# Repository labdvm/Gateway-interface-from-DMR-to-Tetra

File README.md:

# Gateway-interface-from-DMR-to-Tetra
Gateway interface from DMR mobile radio to Tetra MTM5400, Motorola radios
DMR radio communication is via Simplex-Hotspot connect to Brandmeister and DMR RF power should be lowest as possible.
V 1.1
Z32IT

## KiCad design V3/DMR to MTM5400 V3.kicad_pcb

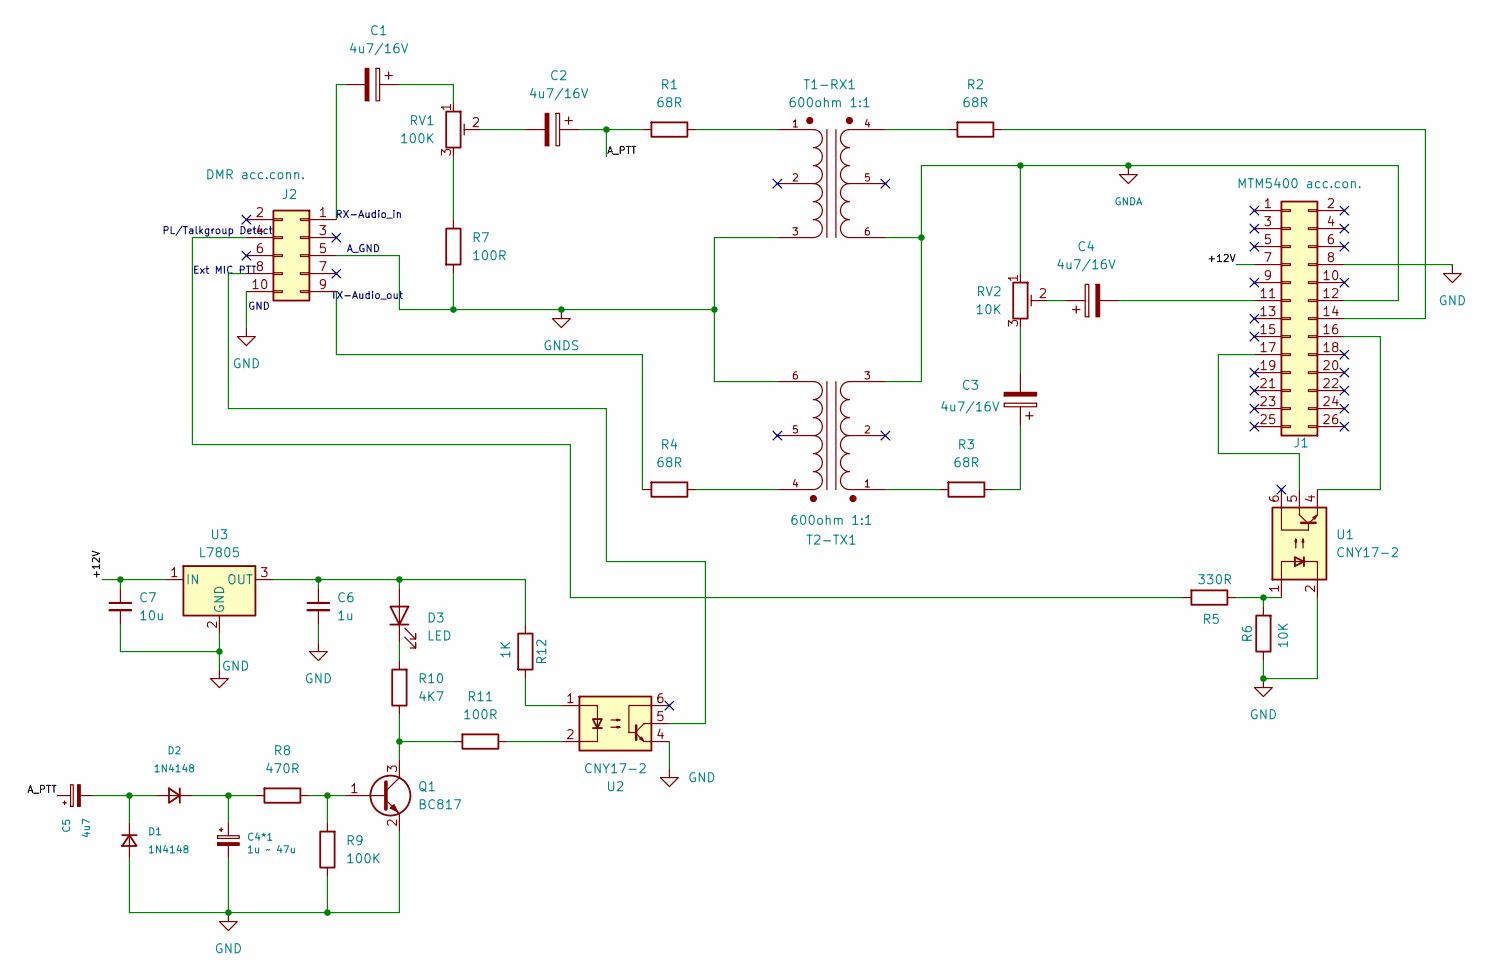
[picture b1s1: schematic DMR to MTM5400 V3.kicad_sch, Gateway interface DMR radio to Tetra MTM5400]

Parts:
C1, C2, C3, C4: 4u7/16V; CP_EIA-3216-12_Kemet-S
C4*1: 1u ~ 47u; CP_EIA-3216-12_Kemet-S
C5: 4u7; CP_EIA-3216-12_Kemet-S
C6: 1u; C_1206_3216Metric
C7: 10u; C_1206_3216Metric
D1, D2: 1N4148; D_SOD-123
D3: LED; LED_1206_3216Metric
J1: MTM5400 acc.con.; MTM5400_1
J2: DMR acc.conn.; PinHeader_2x05_P2.54mm_Vertical
Q1: BC817; SOT-23
R1, R2, R3, R4: 68R; R_1206_3216Metric
R5: 330R; R_1206_3216Metric
R6: 10K; R_1206_3216Metric
R7, R11: 100R; R_1206_3216Metric
R8: 470R; R_1206_3216Metric
R9: 100K; R_1206_3216Metric
R10: 4K7; R_1206_3216Metric
R12: 1K; R_1206_3216Metric
RV1: 100K; Potentiometer_Piher_PT-6-V_Vertical
RV2: 10K; Potentiometer_Piher_PT-6-V_Vertical
T1-RX1, T2-TX1: 600ohm 1:1; XFMR_TY-145P; PARTREV 2016
U1, U2: CNY17-2; DIP-6_W7.62mm_Socket
U3: L7805; TO-252-2

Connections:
/+12V: C7.1, J1.7, U3.1 (IN)
/A_PTT: C2.1, C5.1, R1.2
GND: C4*1.2, C6.2, C7.2, D1.2 (A), J1.8 (GND), J2.10, Q1.2 (E), R6.1, R9.1, U1.2, U2.4, U3.2 (GND)
GNDA: J1.12 (GND_A), RV2.1, T1-RX1.6, T2-TX1.3; also elsewhere on the board
GNDS: J2.5, R7.2, T1-RX1.3, T2-TX1.6; also elsewhere on the board
unnamed: C1.1, RV1.1
unnamed: C2.2, RV1.2
unnamed: C3.1, R3.1
unnamed: C3.2, RV2.3
unnamed: C4.1, RV2.2
unnamed: C5.2, D1.1 (K), D2.2 (A)
unnamed: C4*1.1, D2.1 (K), R8.2
unnamed: C6.1, D3.2 (A), R12.1, U3.3 (OUT)
unnamed: D3.1 (K), R10.2
unnamed: J1.16 (GND_MIC), U1.4
unnamed: J1.17 (PTT), U1.5
unnamed: J1.14 (RX_Audio), R2.1
unnamed: C4.2, J1.11 (TX_Audio)
unnamed: C1.2, J2.1
unnamed: J2.4, R5.2
unnamed: J2.8, U2.5
unnamed: J2.9, R4.2
unnamed: Q1.1 (B), R8.1, R9.2
unnamed: Q1.3 (C), R10.1, R11.2
unnamed 24: R1.1, T1-RX1.1; also elsewhere on the board
unnamed 25: R2.2, T1-RX1.4; also elsewhere on the board
unnamed 26: R3.2, T2-TX1.1; also elsewhere on the board
unnamed 27: R4.1, T2-TX1.4; also elsewhere on the board
unnamed: R5.1, R6.2, U1.1
unnamed: R7.1, RV1.3
unnamed: R11.1, U2.2
unnamed: R12.2, U2.1

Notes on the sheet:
Ext MIC PTT
GND
TX-Audio_out
A_GND
PL/Talkgroup Detect
RX-Audio_in

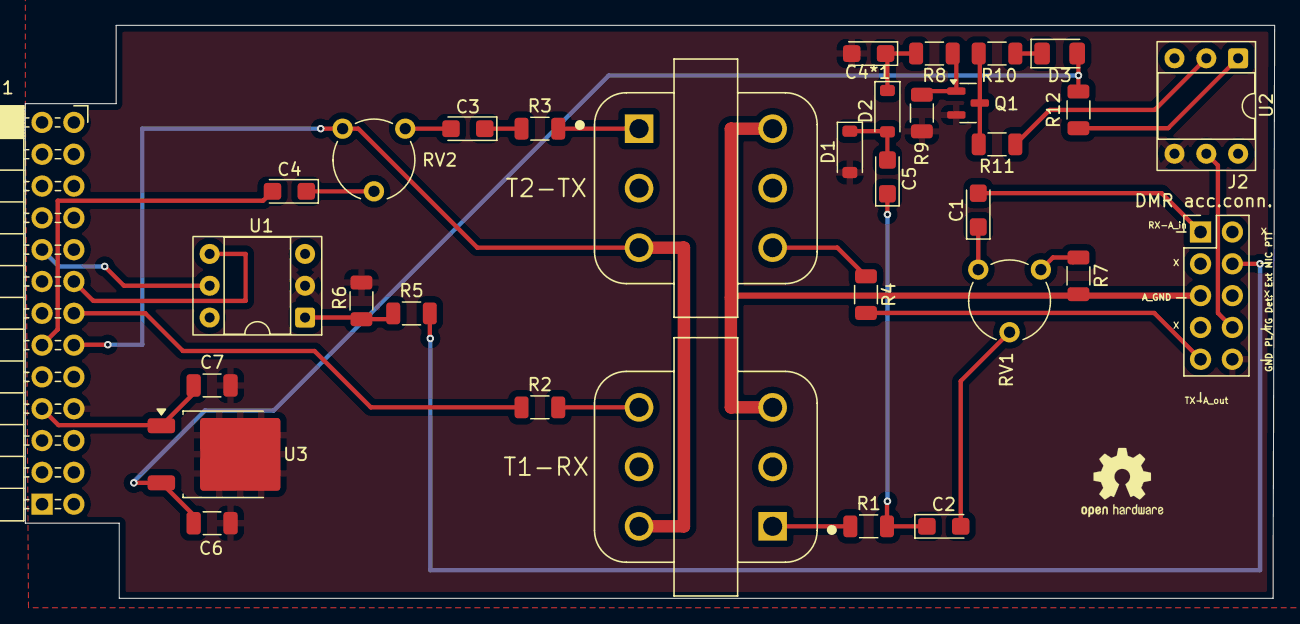
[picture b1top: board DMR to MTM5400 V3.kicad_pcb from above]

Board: 2 copper layers, 99.8 x 45.8 mm, 33 parts (0 on the bottom side), 32 nets.

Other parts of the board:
T1-RX, T2-TX: 600ohm 1:1; XFMR_TY-145P

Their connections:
GNDA: T1-RX.6, T2-TX.3; also elsewhere on the board
GNDS: T1-RX.3, T2-TX.6; also elsewhere on the board
unnamed 24: T1-RX.1; also elsewhere on the board
unnamed 25: T1-RX.4; also elsewhere on the board
unnamed 26: T2-TX.1; also elsewhere on the board
unnamed 27: T2-TX.4; also elsewhere on the board

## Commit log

2026-01-05 Enhance README with DMR communication details
    Added information about DMR radio communication and RF power settings.
